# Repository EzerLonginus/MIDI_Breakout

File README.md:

# MIDI_Breakout
MIDI Breakout for Arduino modules

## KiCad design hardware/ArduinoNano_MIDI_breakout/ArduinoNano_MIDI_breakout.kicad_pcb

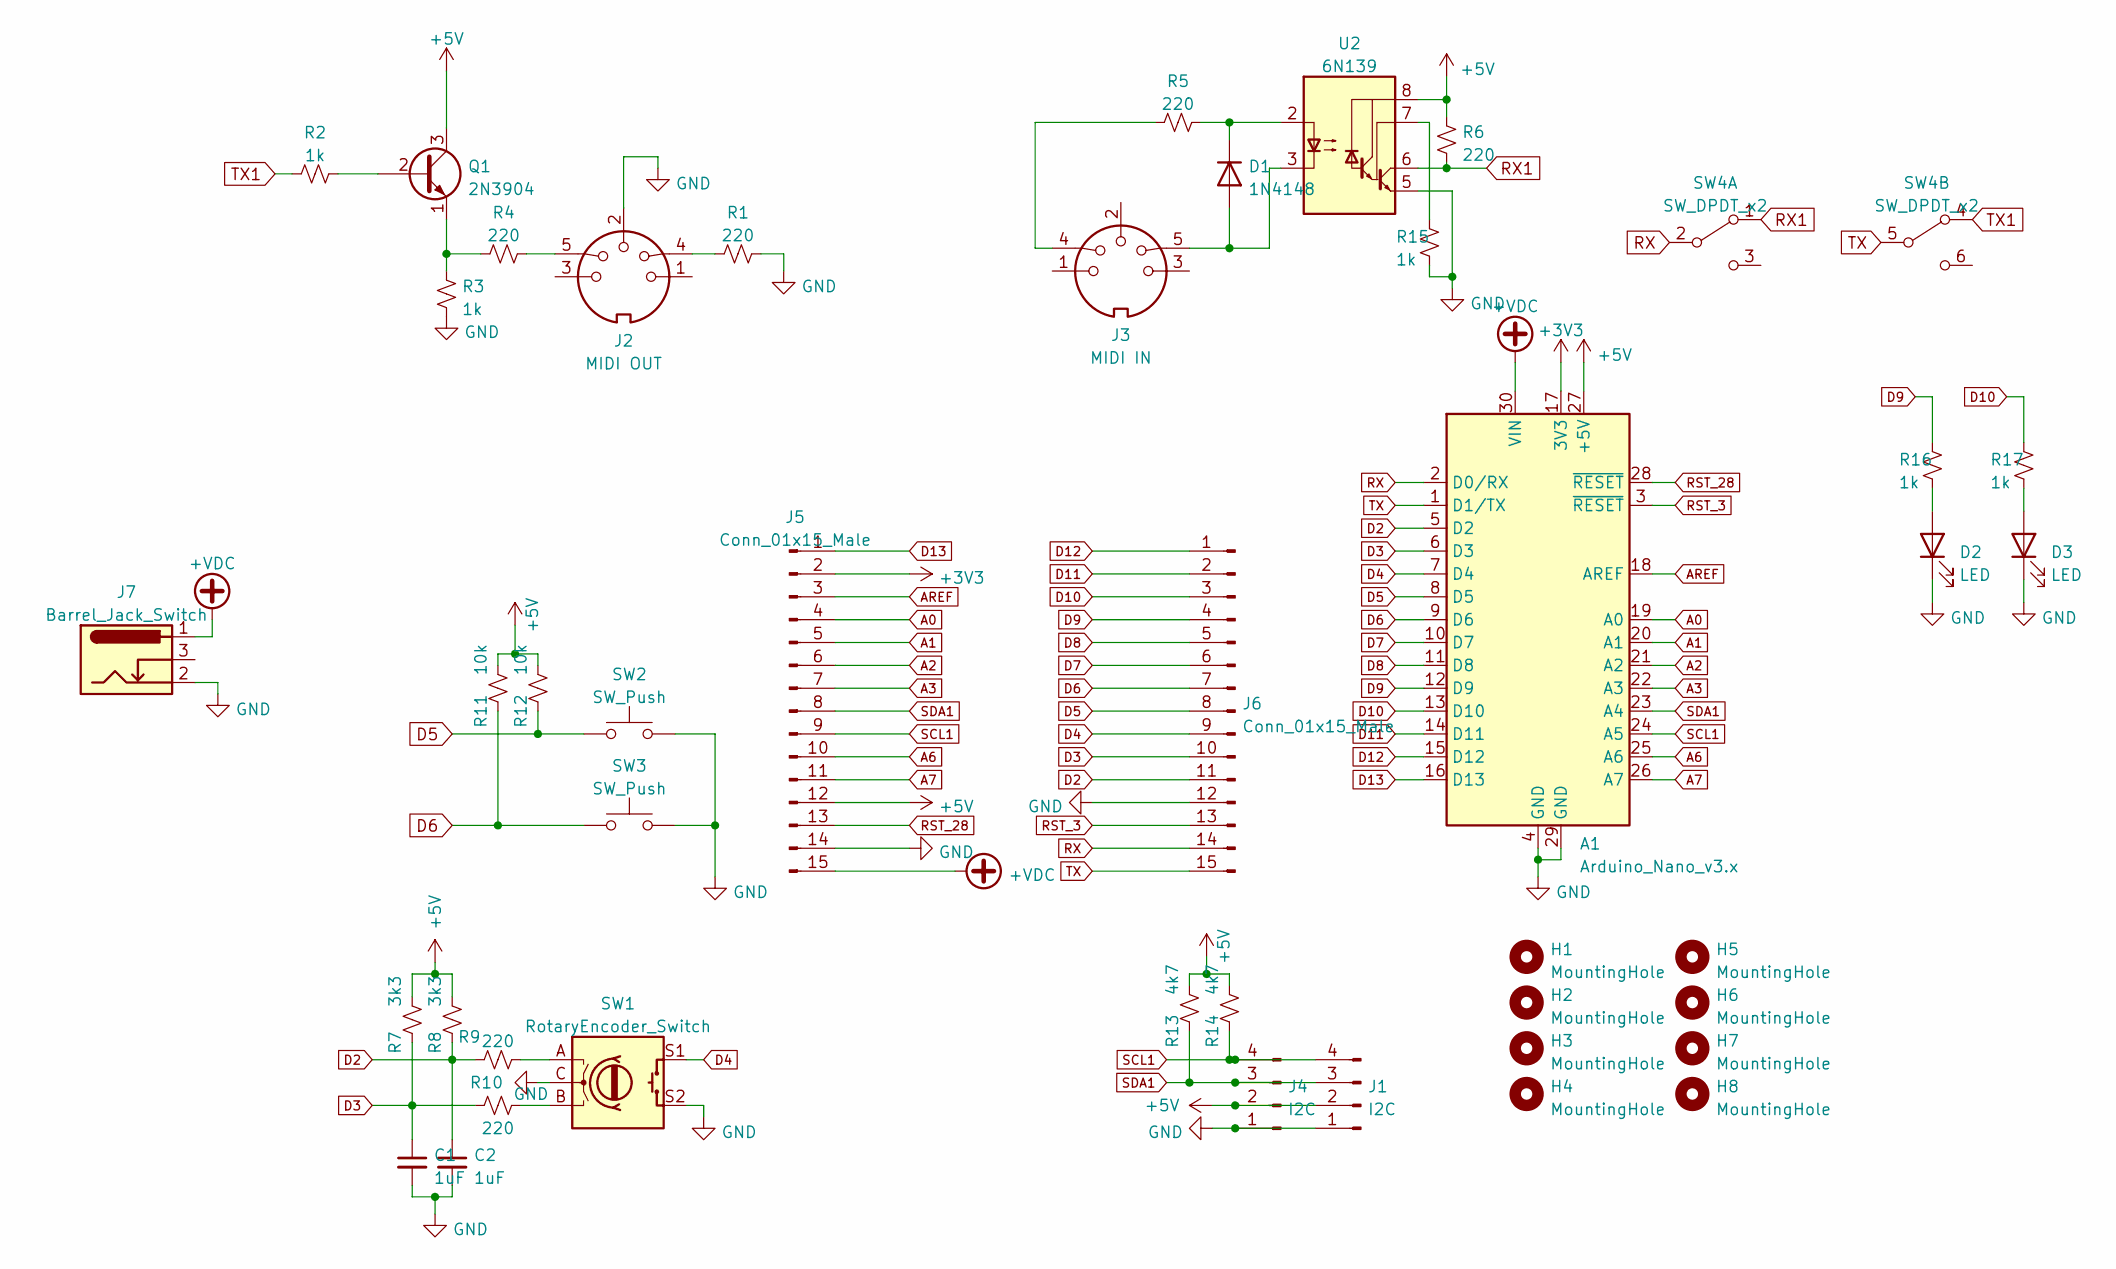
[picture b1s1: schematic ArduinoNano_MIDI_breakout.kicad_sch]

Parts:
A1: Arduino_Nano_v3.x; Arduino_Nano
C1, C2: 1uF; C_Disc_D6.0mm_W4.4mm_P5.00mm
D1: 1N4148; D_DO-35_SOD27_P7.62mm_Horizontal
D2, D3: LED; LED_D5.0mm
H1, H2, H3, H4, H5, H6, H7, H8: MountingHole; MountingHole_3.2mm_M3_DIN965_Pad
J1, J4: I2C; PinHeader_1x04_P2.54mm_Vertical
J2: MIDI OUT; din-5
J3: MIDI IN; din-5
J5, J6: Conn_01x15_Male; PinHeader_1x15_P2.54mm_Vertical
J7: Barrel_Jack_Switch; BarrelJack_GCT_DCJ200-10-A_Horizontal
Q1: 2N3904; TO-92_Inline
R1, R4, R5, R6, R9, R10: 220; R_Axial_DIN0207_L6.3mm_D2.5mm_P7.62mm_Horizontal
R2, R3, R15, R16, R17: 1k; R_Axial_DIN0207_L6.3mm_D2.5mm_P7.62mm_Horizontal
R7, R8: 3k3; R_Axial_DIN0207_L6.3mm_D2.5mm_P7.62mm_Horizontal
R11, R12: 10k; R_Axial_DIN0207_L6.3mm_D2.5mm_P7.62mm_Horizontal
R13, R14: 4k7; R_Axial_DIN0207_L6.3mm_D2.5mm_P7.62mm_Horizontal
SW1: RotaryEncoder_Switch; RotaryEncoder_Alps_EC11E-Switch_Vertical_H20mm
SW2, SW3: SW_Push; SW_PUSH_6mm
SW4: SW_DPDT_x2; SW_CuK_JS202011CQN_DPDT_Straight
U2: 6N139; DIP-8_W7.62mm

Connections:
+3V3: A1.17 (3V3), J5.2
+5V: A1.27 (+5V), J1.2, J4.2, J5.12, Q1.3 (C), R6.2, R7.2, R8.2, R11.2, R12.2, R13.2, R14.2, U2.8 (VCC)
+VDC: A1.30 (VIN), J5.15, J7.1
A0: A1.19 (A0), J5.4
A1: A1.20 (A1), J5.5
A2: A1.21 (A2), J5.6
A3: A1.22 (A3), J5.7
A6: A1.25 (A6), J5.10
A7: A1.26 (A7), J5.11
AREF: A1.18 (AREF), J5.3
D2: A1.5 (D2), C2.1, J6.11, R8.1, R9.1
D3: A1.6 (D3), C1.1, J6.10, R7.1, R10.1
D4: A1.7 (D4), J6.9, SW1.S1
D5: A1.8 (D5), J6.8, R12.1, SW2.1
D6: A1.9 (D6), J6.7, R11.1, SW3.1
D7: A1.10 (D7), J6.6
D8: A1.11 (D8), J6.5
D9: A1.12 (D9), J6.4, R16.1
D10: A1.13 (D10), J6.3, R17.1
D11: A1.14 (D11), J6.2
D12: A1.15 (D12), J6.1
D13: A1.16 (D13), J5.1
GND: A1.4 (GND), A1.29 (GND), C1.2, C2.2, D2.1 (K), D3.1 (K), J1.1, J2.2, J4.1, J5.14, J6.12, J7.2, R1.2, R3.2, R15.2, SW1.C, SW1.S2, SW2.2, SW3.2, U2.5 (GND)
unnamed: D1.2 (A), J3.5, U2.3 (C2)
unnamed: D1.1 (K), R5.2, U2.2 (C1)
unnamed: D2.2 (A), R16.2
unnamed: D3.2 (A), R17.2
unnamed: J2.4, R1.1
unnamed: J2.5, R4.2
unnamed: J3.4, R5.1
unnamed: Q1.2 (B), R2.2
unnamed: Q1.1 (E), R3.1, R4.1
unnamed: R9.2, SW1.A
unnamed: R10.2, SW1.B
unnamed: R15.1, U2.7 (VO1)
RST_3: A1.3 (~RESET), J6.13
RST_28: A1.28 (~RESET), J5.13
RX: A1.2 (D0/RX), J6.14, SW4.2 (B)
RX1: R6.1, SW4.1 (A), U2.6 (VO2)
SCL1: A1.24 (A5), J1.4, J4.4, J5.9, R14.1
SDA1: A1.23 (A4), J1.3, J4.3, J5.8, R13.1
TX: A1.1 (D1/TX), J6.15, SW4.5 (B)
TX1: R2.1, SW4.4 (A)

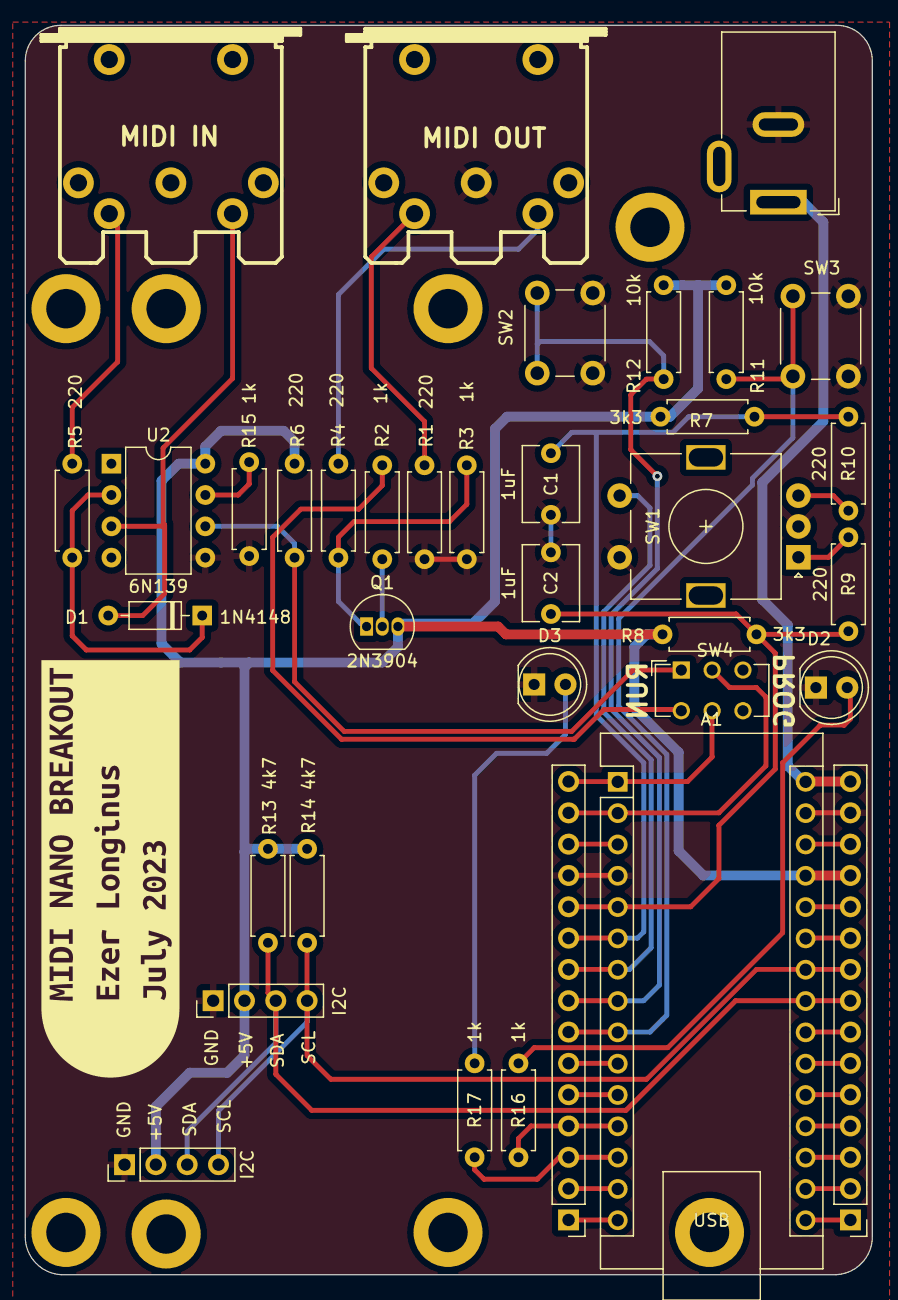
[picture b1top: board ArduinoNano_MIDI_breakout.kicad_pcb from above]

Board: 2 copper layers, 68.7 x 101.3 mm, 45 parts (0 on the bottom side), 43 nets.

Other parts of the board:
kibuzzard-64B16D4A: G***; kibuzzard-64B16D4A

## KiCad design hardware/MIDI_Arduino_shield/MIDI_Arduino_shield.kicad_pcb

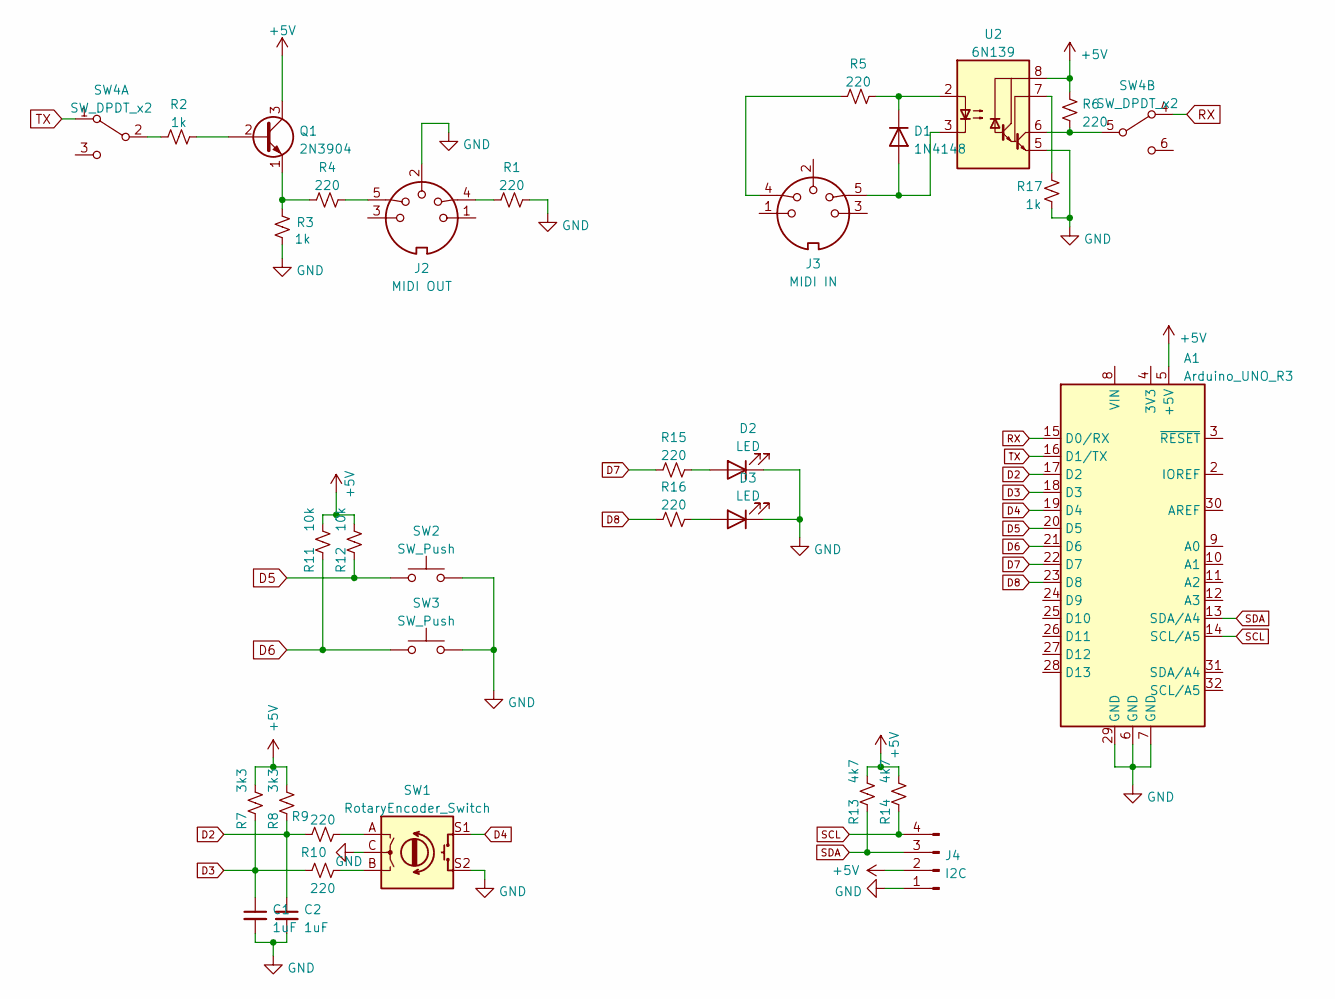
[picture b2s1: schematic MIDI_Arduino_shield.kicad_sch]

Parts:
A1: Arduino_UNO_R3
C1, C2: 1uF; C_Disc_D6.0mm_W4.4mm_P5.00mm
D1: 1N4148; D_DO-35_SOD27_P7.62mm_Horizontal
D2, D3: LED; LED_D5.0mm
J2: MIDI OUT; din-5
J3: MIDI IN; din-5
J4: I2C; PinHeader_1x04_P2.54mm_Vertical
Q1: 2N3904; TO-92_Inline
R1, R4, R5, R6, R9, R10, R15, R16: 220; R_Axial_DIN0207_L6.3mm_D2.5mm_P7.62mm_Horizontal
R2, R3, R17: 1k; R_Axial_DIN0207_L6.3mm_D2.5mm_P7.62mm_Horizontal
R7, R8: 3k3; R_Axial_DIN0207_L6.3mm_D2.5mm_P7.62mm_Horizontal
R11, R12: 10k; R_Axial_DIN0207_L6.3mm_D2.5mm_P7.62mm_Horizontal
R13, R14: 4k7; R_Axial_DIN0207_L6.3mm_D2.5mm_P7.62mm_Horizontal
SW1: RotaryEncoder_Switch; RotaryEncoder_Alps_EC11E-Switch_Vertical_H20mm
SW2, SW3: SW_Push; SW_PUSH_6mm
SW4: SW_DPDT_x2; SW_CuK_JS202011CQN_DPDT_Straight
U2: 6N139; DIP-8_W7.62mm

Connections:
+5V: A1.5 (+5V), J4.2, Q1.3 (C), R6.2, R7.2, R8.2, R11.2, R12.2, R13.2, R14.2, U2.8 (VCC)
D2: A1.17 (D2), C2.1, R8.1, R9.1
D3: A1.18 (D3), C1.1, R7.1, R10.1
D4: A1.19 (D4), SW1.S1
D5: A1.20 (D5), R12.1, SW2.1
D6: A1.21 (D6), R11.1, SW3.1
D7: A1.22 (D7), R15.1
D8: A1.23 (D8), R16.1
GND: A1.6 (GND), A1.7 (GND), A1.29 (GND), C1.2, C2.2, D2.1 (K), D3.1 (K), J2.2, J4.1, R1.2, R3.2, R17.2, SW1.C, SW1.S2, SW2.2, SW3.2, U2.5 (GND)
unnamed: D1.1 (K), R5.2, U2.2 (C1)
unnamed: D1.2 (A), J3.5, U2.3 (C2)
unnamed: D2.2 (A), R15.2
unnamed: D3.2 (A), R16.2
unnamed: J2.4, R1.1
unnamed: J2.5, R4.2
unnamed: J3.4, R5.1
unnamed: Q1.1 (E), R3.1, R4.1
unnamed: Q1.2 (B), R2.2
unnamed: R2.1, SW4.2 (B)
unnamed: R6.1, SW4.5 (B), U2.6 (VO2)
unnamed: R9.2, SW1.A
unnamed: R10.2, SW1.B
unnamed: R17.1, U2.7 (VO1)
RX: A1.15 (D0/RX), SW4.4 (A)
SCL: A1.14 (SCL/A5), J4.4, R14.1
SDA: A1.13 (SDA/A4), J4.3, R13.1
TX: A1.16 (D1/TX), SW4.1 (A)

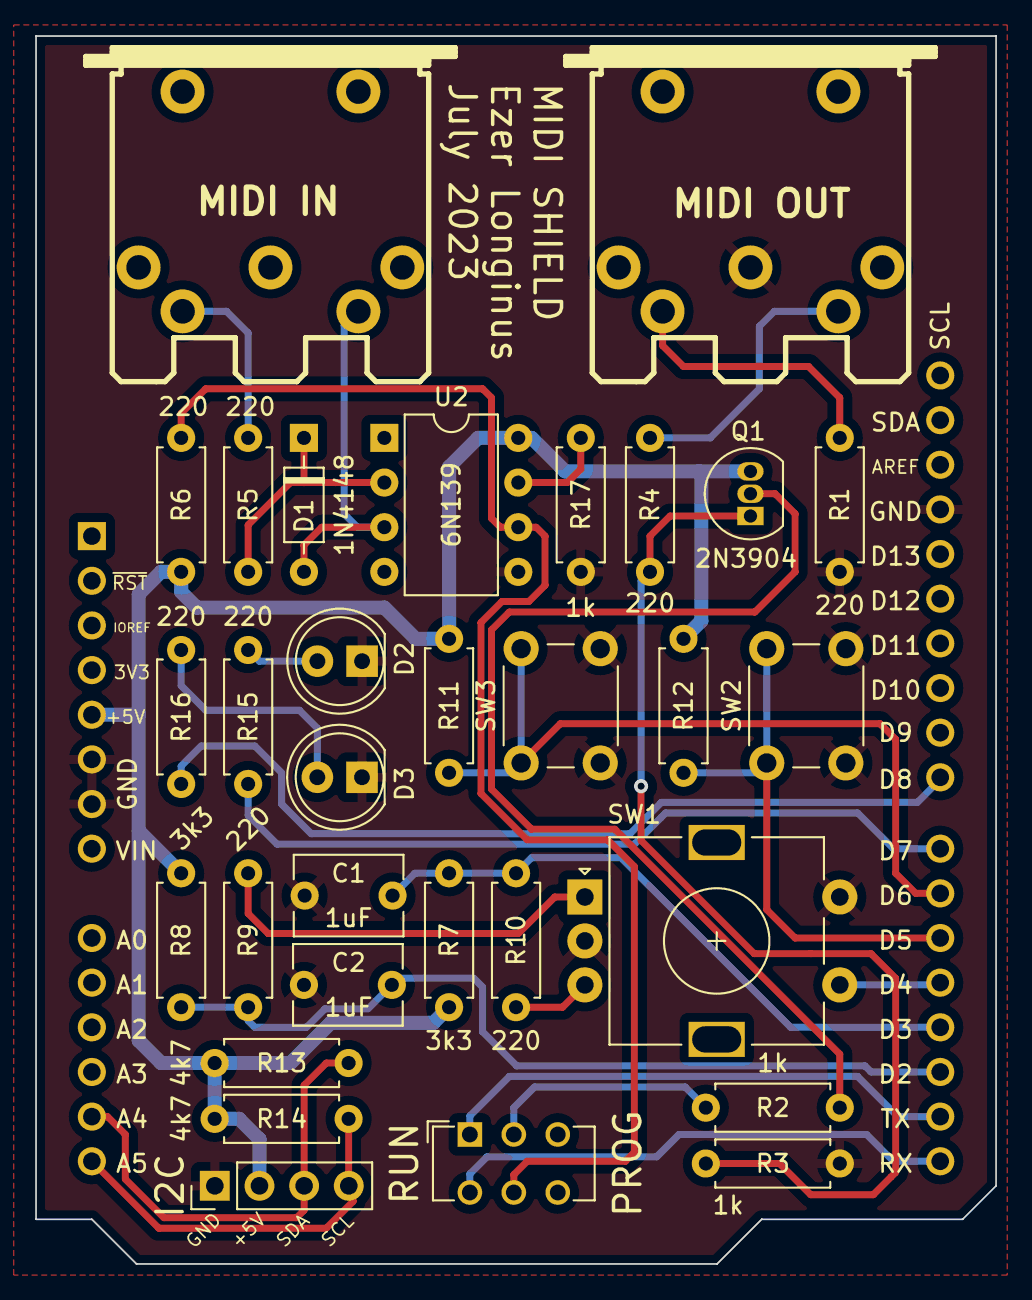
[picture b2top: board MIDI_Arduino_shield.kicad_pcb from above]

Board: 2 copper layers, 54.6 x 69.8 mm, 32 parts (1 on the bottom side), 27 nets.

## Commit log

2023-06-19 MIDI Breakout Variations
2023-07-10 Fixed MIDI pinout swap
2023-08-10 Fixes to Nano Breakout
